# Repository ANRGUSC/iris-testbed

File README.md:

# iris-testbed
Intelligent Robotic Internet of Things TeStbed (IRIS) - Links and Documentation

Autonomous Networks Research Group (ANRG)

University of Southern California

Welcome to the main IRIS repository where you can find the code, documentation, 
and pcb designs related to the open source IRIS testbed. There are many modular 
parts of the IRIS testbed that may be useful for researchers, and, because the 
maintainers are currently low on bandwidth, we ask strongly encourage the 
community to please submit a Github issue to request further documentation or 
help on how to recreate any to all parts  of the IRIS testbed.

## Repositories:

[IRIS-RIOT](https://github.com/ANRGUSC/iris-riot) - A fork of RIOT-OS with all 
RIOT related IRIS testbed application code.

[IRIS-mbed-os-3pi](https://github.com/ANRGUSC/iris-mbed-os-3pi) - IRIS testbed
application code built on mbed OS for the mbed LPC1768 platform and code for
the Pololu 3pi base (atmega328p MCU).

One very useful piece to the community is the IRISbot's MCU to MCU communication 
via HDLC over UART. We have implemented cross-comaptible libraries for both 
RIOT-OS and mbed OS for sending HDLC packets in a multi-threaded environment.
For the RIOT-OS implementation:

[RIOT-OS HDLC Implementation](https://github.com/ANRGUSC/iris-riot/tree/develop/sys/net/link_layer/hdlc)

[RIOT-OS HDLC Tests](https://github.com/ANRGUSC/iris-riot/tree/develop/examples/iris_testbed/tests/hdlc_txvr)

For the mbed OS implementation:

[mbed OS HDLC Implementation](https://github.com/ANRGUSC/iris-mbed-os-3pi/blob/develop/hdlc.cpp)

[mbed OS HDLC Tests](https://github.com/ANRGUSC/iris-mbed-os-3pi/tree/develop/app_files/hdlc_test)

## PCB Designs

Please see the `pcb_designs` folder to find the .brd and .sch files (Eagle) of 
the various PCB designs for the IRISbots. Since the publishing of our original
paper, we have upgraded the triple sensor board to a quadruple sensor board 
because we found using three sensors for omnidirectional localization resulted
in sporadic blindspots. The layouts have also been simplified to reduce the 
number of needed jumper cables. To manufacture our PCB designs, we suggest using 
[seeedstudio.io](https://www.seeedstudio.io/).

## Video Links

[IRIS Trilateration](https://www.youtube.com/watch?v=-iA_I1HjI5E)

[IRIS Chain Test](https://www.youtube.com/watch?v=XQomuFSqbBQ)

## IROS 2018 Presentation Slides:

https://docs.google.com/presentation/d/1Dmg364Kt8fulA3RI1eVobmNLkZHoMGymSkHf-HZB2n8/edit?usp=sharing

## References:

Jason A Tran, Pradipta Ghosh, Yutong Gu, Richard Kim, Daniel D’Souza, Nora 
Ayanian, Bhaskar Krishnamachari, 
"[Intelligent Robotic IoT System (IRIS) Testbed](https://anrg.usc.edu/www/wp-content/uploads/2018/09/Intelligent_Robotic_Iot_System_Testbed__IRIS_-4.pdf)",
in IEEE/RSJ International Conference on Intelligent Robots and Systems (IROS), 
Oct, 2018.

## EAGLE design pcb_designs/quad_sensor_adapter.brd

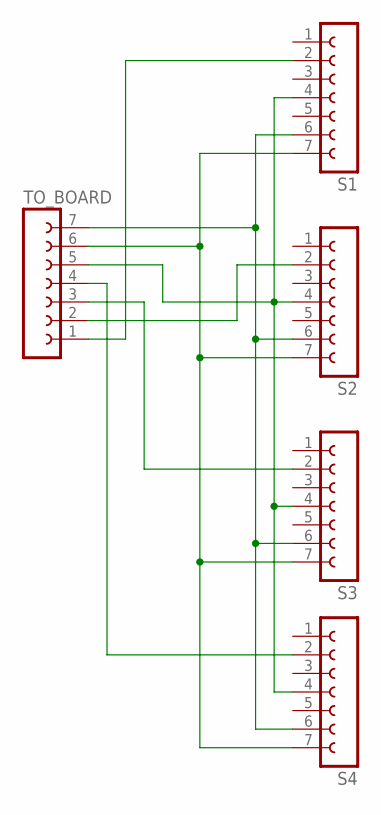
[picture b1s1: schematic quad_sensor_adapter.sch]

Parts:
S1, S2, S3, S4: FE07-1; FE07
TO_BOARD: FE07-1; FE07

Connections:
GRND: S1.7, S2.7, S3.7, S4.7, TO_BOARD.6
unnamed: S4.2, TO_BOARD.4
PWR: S1.6, S2.6, S3.6, S4.6, TO_BOARD.7
RX1: S1.2, TO_BOARD.1
RX2: S2.2, TO_BOARD.2
RX3: S3.2, TO_BOARD.3
S3: S1.4, S2.4, S3.4, S4.4, TO_BOARD.5

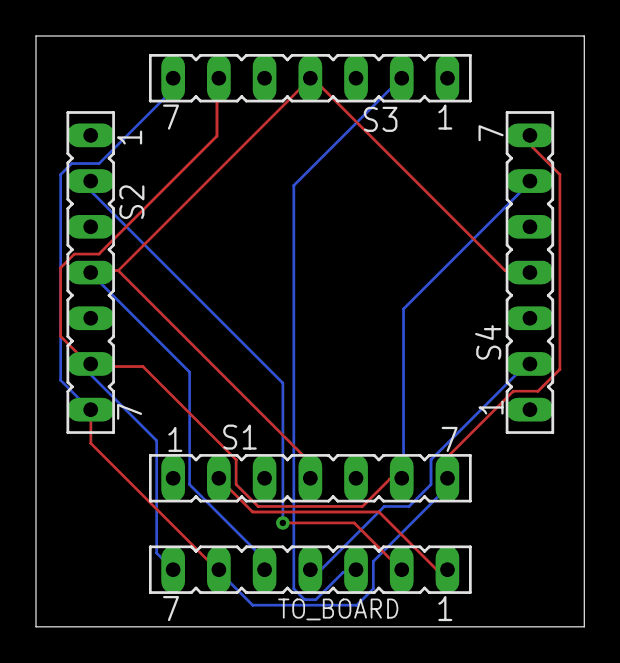
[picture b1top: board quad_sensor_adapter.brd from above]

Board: 2 copper layers, 30.5 x 32.8 mm, 5 parts (0 on the bottom side), 7 nets.

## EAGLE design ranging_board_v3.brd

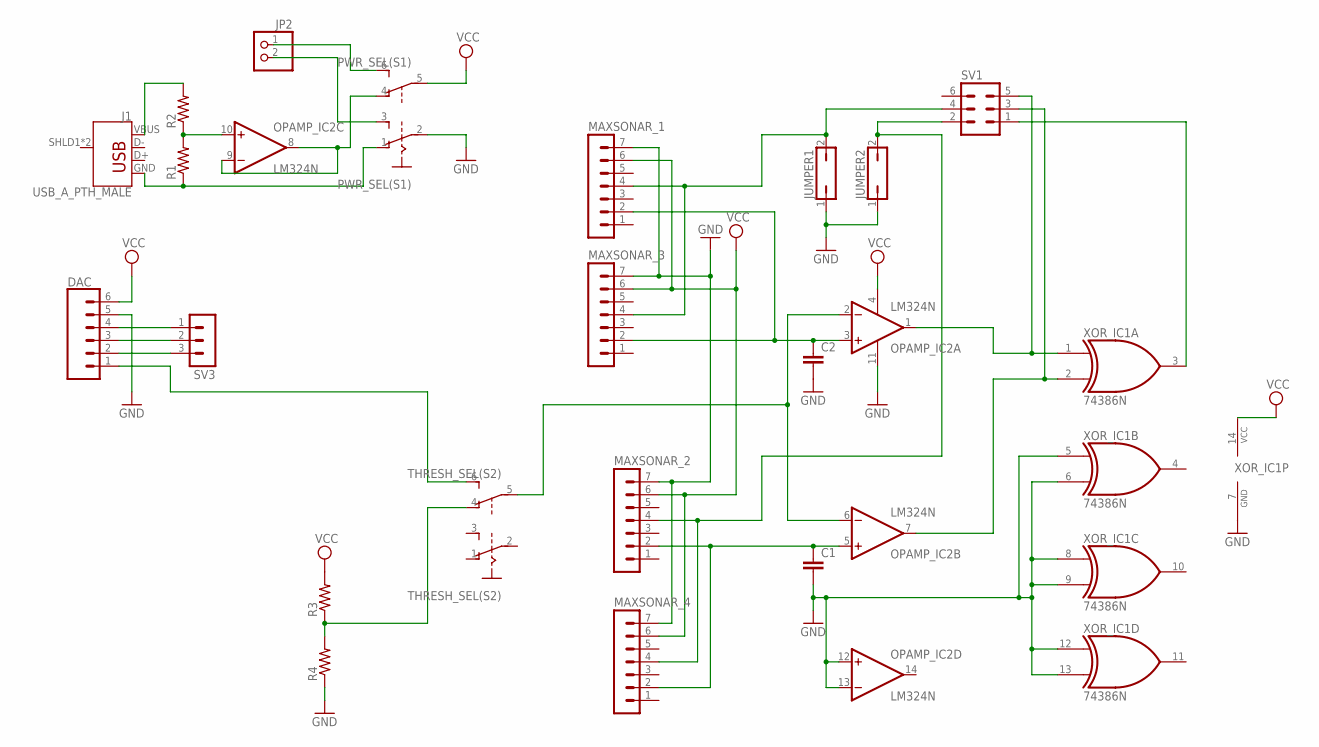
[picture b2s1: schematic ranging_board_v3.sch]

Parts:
C1, C2: C5/3; C5B3
DAC: CONN_06SILK_FEMALE_PTH; 1X06
J1: USB_A_PTH_MALE; USB-A-H
JP2: PINHD-1X2; 1X02
JUMPER1, JUMPER2: JP1Q; JP1
MAXSONAR_1, MAXSONAR_2, MAXSONAR_3, MAXSONAR_4: MA07-1
OPAMP_IC2: LM324N; DIL14
PWR_SEL(S1): A68-A31
R1, R2, R3, R4: R-US_0204/7; 0204/7
SV1: MA03-2
SV3: MA03-1
THRESH_SEL(S2): A68-A31
XOR_IC1: 74386N; DIL14

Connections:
GND: C1.2, C2.2, DAC.5, JUMPER1.1, JUMPER2.1, MAXSONAR_1.7, MAXSONAR_2.7, MAXSONAR_3.7, MAXSONAR_4.7, OPAMP_IC2.11 (V-), OPAMP_IC2.12 (+IN), OPAMP_IC2.13 (-IN), PWR_SEL(S1).2, R4.1, XOR_IC1.5 (I0), XOR_IC1.6 (I1), XOR_IC1.7 (GND), XOR_IC1.8 (I0), XOR_IC1.9 (I1), XOR_IC1.12 (I0), XOR_IC1.13 (I1)
unnamed: R3.1, R4.2, THRESH_SEL(S2).4 (O)
unnamed: DAC.4, SV3.1
unnamed: DAC.2, SV3.3
unnamed: DAC.3, SV3.2
unnamed: DAC.1, THRESH_SEL(S2).6 (S)
unnamed: OPAMP_IC2.10 (+IN), R1.2, R2.1
unnamed: J1.VBUS, R2.2
unnamed: OPAMP_IC2.8 (OUT), OPAMP_IC2.9 (-IN), PWR_SEL(S1).4 (O)
unnamed: J1.GND, PWR_SEL(S1).1 (O), R1.1
unnamed: JP2.2, PWR_SEL(S1).3 (S)
unnamed: JP2.1, PWR_SEL(S1).6 (S)
RX_1: C2.1, MAXSONAR_1.2, MAXSONAR_3.2, OPAMP_IC2.3 (+IN)
RX_2: C1.1, MAXSONAR_2.2, MAXSONAR_4.2, OPAMP_IC2.5 (+IN)
RX_PIN1: OPAMP_IC2.1 (OUT), SV1.5, XOR_IC1.1 (I0)
RX_PIN2: OPAMP_IC2.7 (OUT), SV1.3, XOR_IC1.2 (I1)
THRESH: OPAMP_IC2.2 (-IN), OPAMP_IC2.6 (-IN), THRESH_SEL(S2).5
TX_1: JUMPER1.2, MAXSONAR_1.4, MAXSONAR_3.4, SV1.4
TX_2: JUMPER2.2, MAXSONAR_2.4, MAXSONAR_4.4, SV1.2
VCC: DAC.6, MAXSONAR_1.6, MAXSONAR_2.6, MAXSONAR_3.6, MAXSONAR_4.6, OPAMP_IC2.4 (V+), PWR_SEL(S1).5, R3.2, XOR_IC1.14 (VCC)
XOR_PIN: SV1.1, XOR_IC1.3 (O)

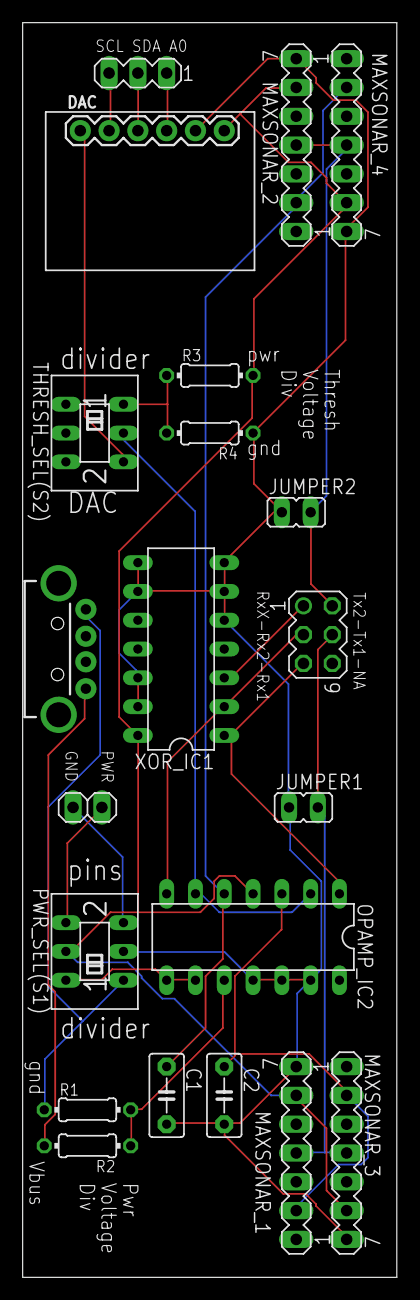
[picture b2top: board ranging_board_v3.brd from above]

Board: 2 copper layers, 33.0 x 110.7 mm, 21 parts (0 on the bottom side), 21 nets.

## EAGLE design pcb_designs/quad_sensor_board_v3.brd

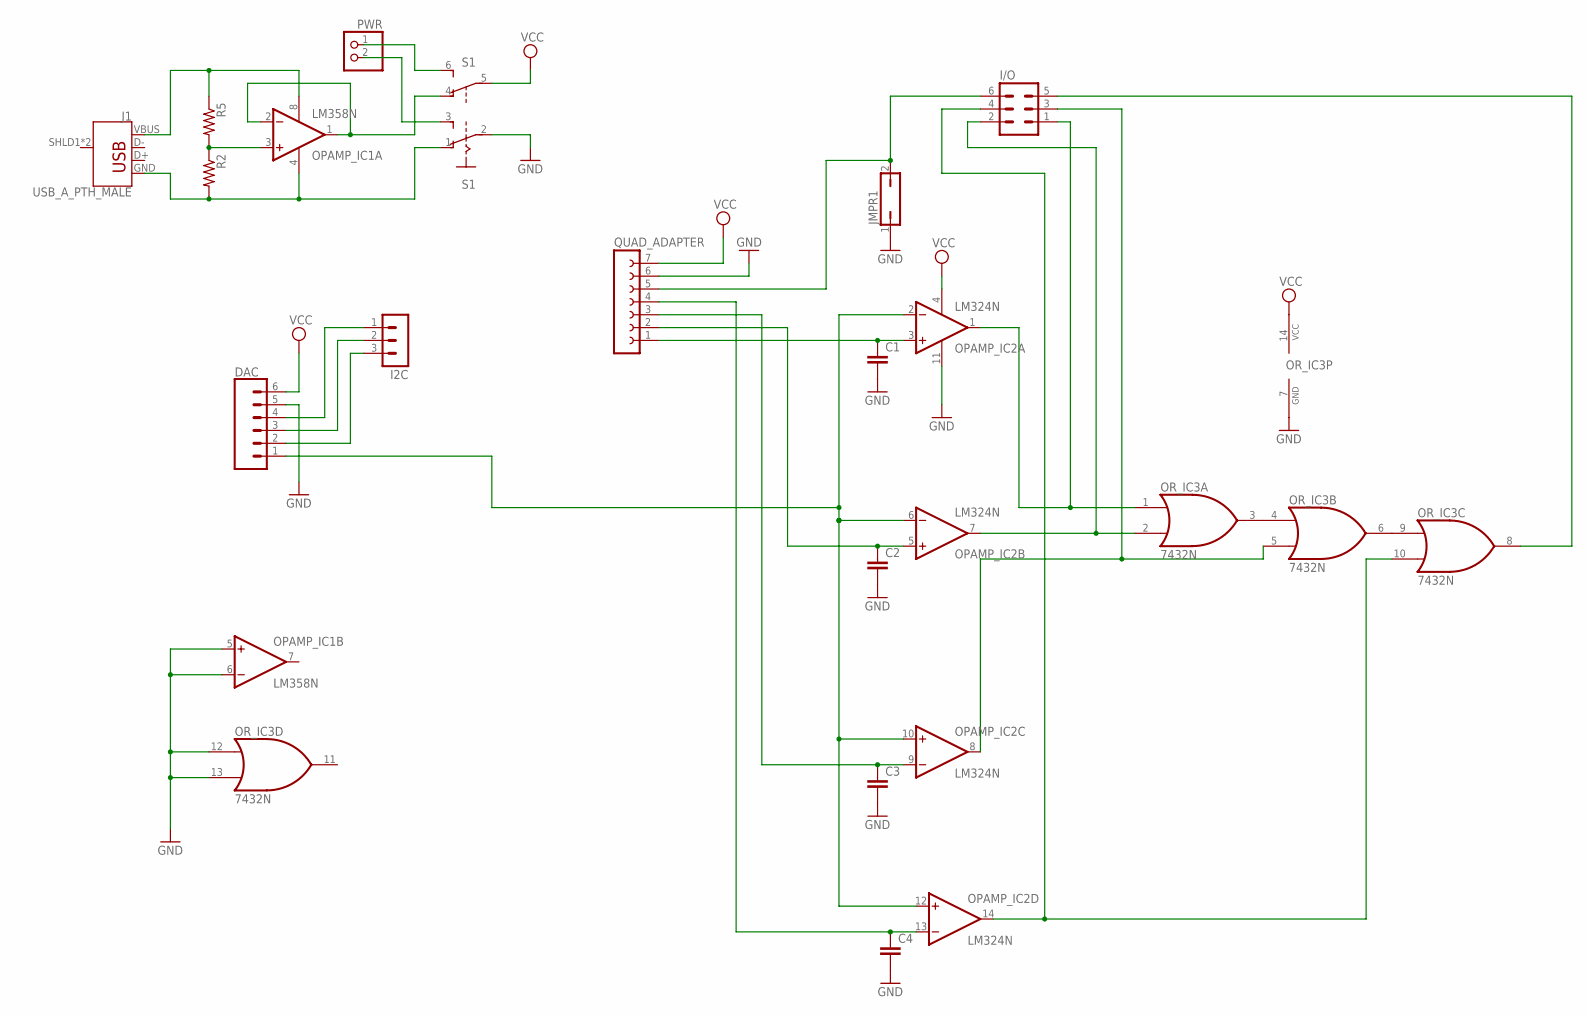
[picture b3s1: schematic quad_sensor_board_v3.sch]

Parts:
C1, C2, C3, C4: C5/3; C5B3
DAC: CONN_06NO_SILK_NO_POP; 1X06_NO_SILK
I2C: MA03-1
I/O: MA03-2
J1: USB_A_PTH_MALE; USB-A-H
JMPR1: JP1Q; JP1
OPAMP_IC1: LM358N; DIL08
OPAMP_IC2: LM324N; DIL14
OR_IC3: 7432N; DIL14
PWR: PINHD-1X2; 1X02
QUAD_ADAPTER: FE07-1; FE07
R2, R5: R-US_0204/7; 0204/7
S1: A68-A31

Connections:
GND: C1.2, C2.2, C3.2, C4.2, DAC.5, JMPR1.1, OPAMP_IC1.5 (+IN), OPAMP_IC1.6 (-IN), OPAMP_IC2.11 (V-), OR_IC3.7 (GND), OR_IC3.12 (I0), OR_IC3.13 (I1), QUAD_ADAPTER.6, S1.2
unnamed: OPAMP_IC1.3 (+IN), R2.1, R5.2
unnamed: J1.VBUS, OPAMP_IC1.8 (V+), R5.1
unnamed: OR_IC3.3 (O), OR_IC3.4 (I0)
unnamed: I/O.4, OPAMP_IC2.14 (OUT), OR_IC3.10 (I1)
unnamed: OPAMP_IC1.1 (OUT), OPAMP_IC1.2 (-IN), S1.4 (O)
unnamed: OR_IC3.6 (O), OR_IC3.9 (I0)
unnamed: DAC.4, I2C.1
unnamed: DAC.3, I2C.2
unnamed: DAC.2, I2C.3
unnamed: I/O.1, OPAMP_IC2.1 (OUT), OR_IC3.1 (I0)
unnamed: J1.GND, OPAMP_IC1.4 (V-), R2.2, S1.1 (O)
unnamed: PWR.2, S1.3 (S)
unnamed: PWR.1, S1.6 (S)
OR_PIN: I/O.5, OR_IC3.8 (O)
RX_1: C1.1, OPAMP_IC2.3 (+IN), QUAD_ADAPTER.1
RX_2: C2.1, OPAMP_IC2.5 (+IN), QUAD_ADAPTER.2
RX_3: C3.1, OPAMP_IC2.9 (-IN), QUAD_ADAPTER.3
RX_4: C4.1, OPAMP_IC2.13 (-IN), QUAD_ADAPTER.4
RX_PIN1: I/O.3, OPAMP_IC2.8 (OUT), OR_IC3.5 (I1)
RX_PIN2: I/O.2, OPAMP_IC2.7 (OUT), OR_IC3.2 (I1)
THRESH: DAC.1, OPAMP_IC2.2 (-IN), OPAMP_IC2.6 (-IN), OPAMP_IC2.10 (+IN), OPAMP_IC2.12 (+IN)
TX_1: I/O.6, JMPR1.2, QUAD_ADAPTER.5
VCC: DAC.6, OPAMP_IC2.4 (V+), OR_IC3.14 (VCC), QUAD_ADAPTER.7, S1.5

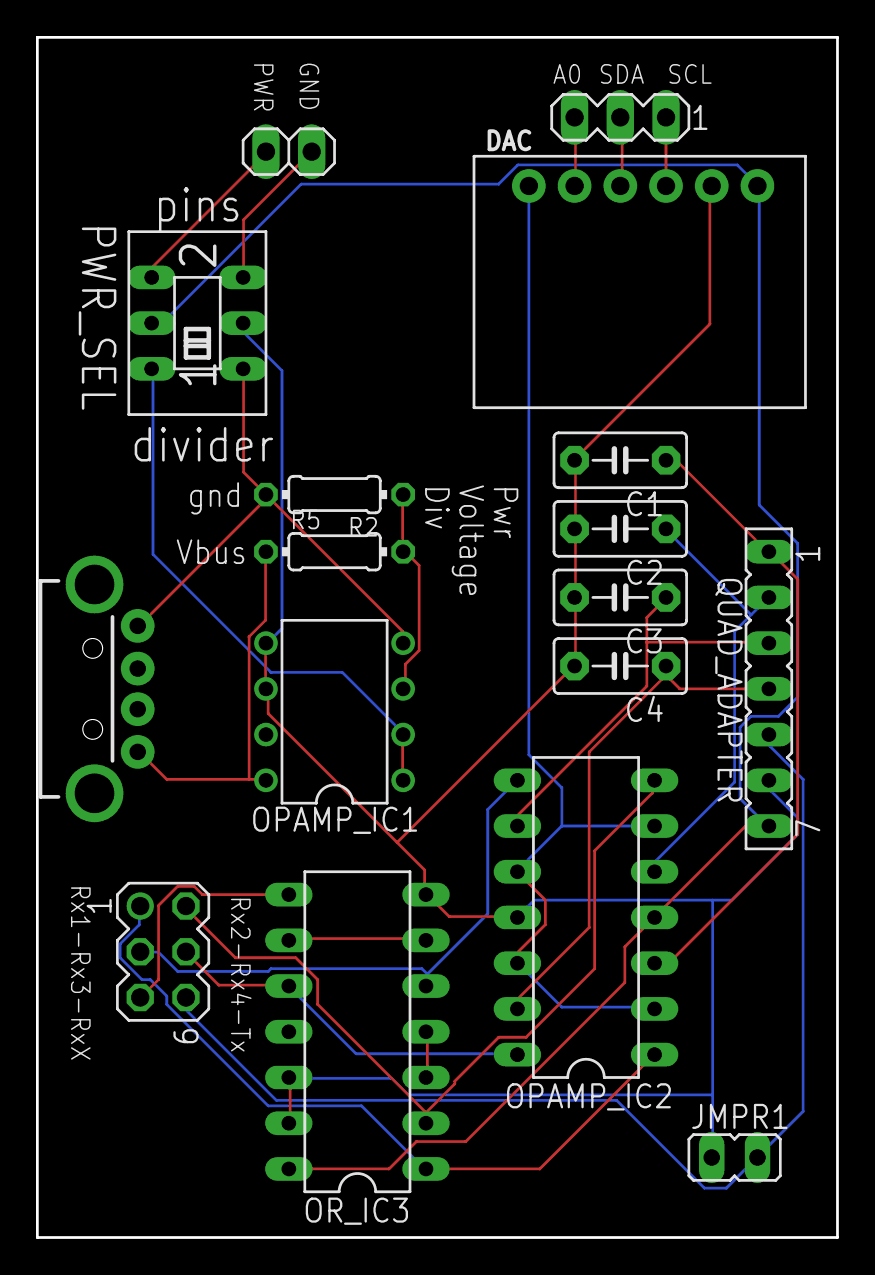
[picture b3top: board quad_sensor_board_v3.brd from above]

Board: 2 copper layers, 44.5 x 66.7 mm, 17 parts (0 on the bottom side), 24 nets.

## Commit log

2018-09-28 README updates and LICENSE init commit
2019-01-22 add pcb designs
2019-01-22 update readme and license
2019-01-22 add links to HDLC implementation in README.md
2019-01-22 add notes on PCB manufacturing

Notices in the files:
parts and their libraries:
SparkFun-Connectors: Licensing: Creative Commons ShareAlike 4.0 International - https://creativecommons.org/licenses/by-sa/4.0
